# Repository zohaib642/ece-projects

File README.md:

# ece-projects

**Street Fighter (MSPM0G3507 Embedded Game)**
A 1v1 fighting game running on a custom PCB designed in KiCad and hand-soldered. Built around the MSPM0G3507 microcontroller with custom hardware drivers and a 30 Hz game engine running on a TimerG12 ISR. Player movement is driven by a slidepot ADC channel, a 2-axis analog joystick handles jumping, and four external buttons map to punch, kick, block, and pause. Sampled audio plays through a 5-bit DAC over an 11 kHz SysTick interrupt, providing background music and event-driven sound effects (hit, block, KO). Features include 16-bit color sprite rendering on an ST7735 LCD with edge-only erase to minimize flicker, an enemy AI with attack/block/movement states, real-time HP and score tracking, and bilingual (English/Spanish) UI selectable at startup.

**Programmable Stopwatch/Timer (Verilog on Basys3 FPGA)**
A four-mode digital stopwatch and countdown timer implemented in Verilog using RTL-design methodology and deployed to a Digilent Basys3 FPGA. Designed via HLSM formalism with a custom datapath and controller FSM. Supports counting up from 00.00, counting down from 99.99, and externally loaded variants where the initial seconds value is set through eight onboard switches. Time is shown across four seven-segment displays at 10 ms resolution, with two pushbuttons for start/stop and reset and two mode-select switches. Built and verified in Xilinx Vivado.

**Buck Converter (PWM Control)**
Design and analysis of a DC-DC buck converter circuit using PWM control. Explores the relationship between switching frequency (50-100 kHz), duty cycle, and output voltage regulation. Includes current sensing measurements and characterization of the linear relationship between op-amp output and load voltage.

**Stone Game (LC-3 Assembly)**
A two-player Nim-style strategy game implemented in LC-3 assembly language. Players alternate removing stones from three rows (A, B, C), with the player who takes the last stone winning. Features input validation, game state management, and a complete turn-based game loop.

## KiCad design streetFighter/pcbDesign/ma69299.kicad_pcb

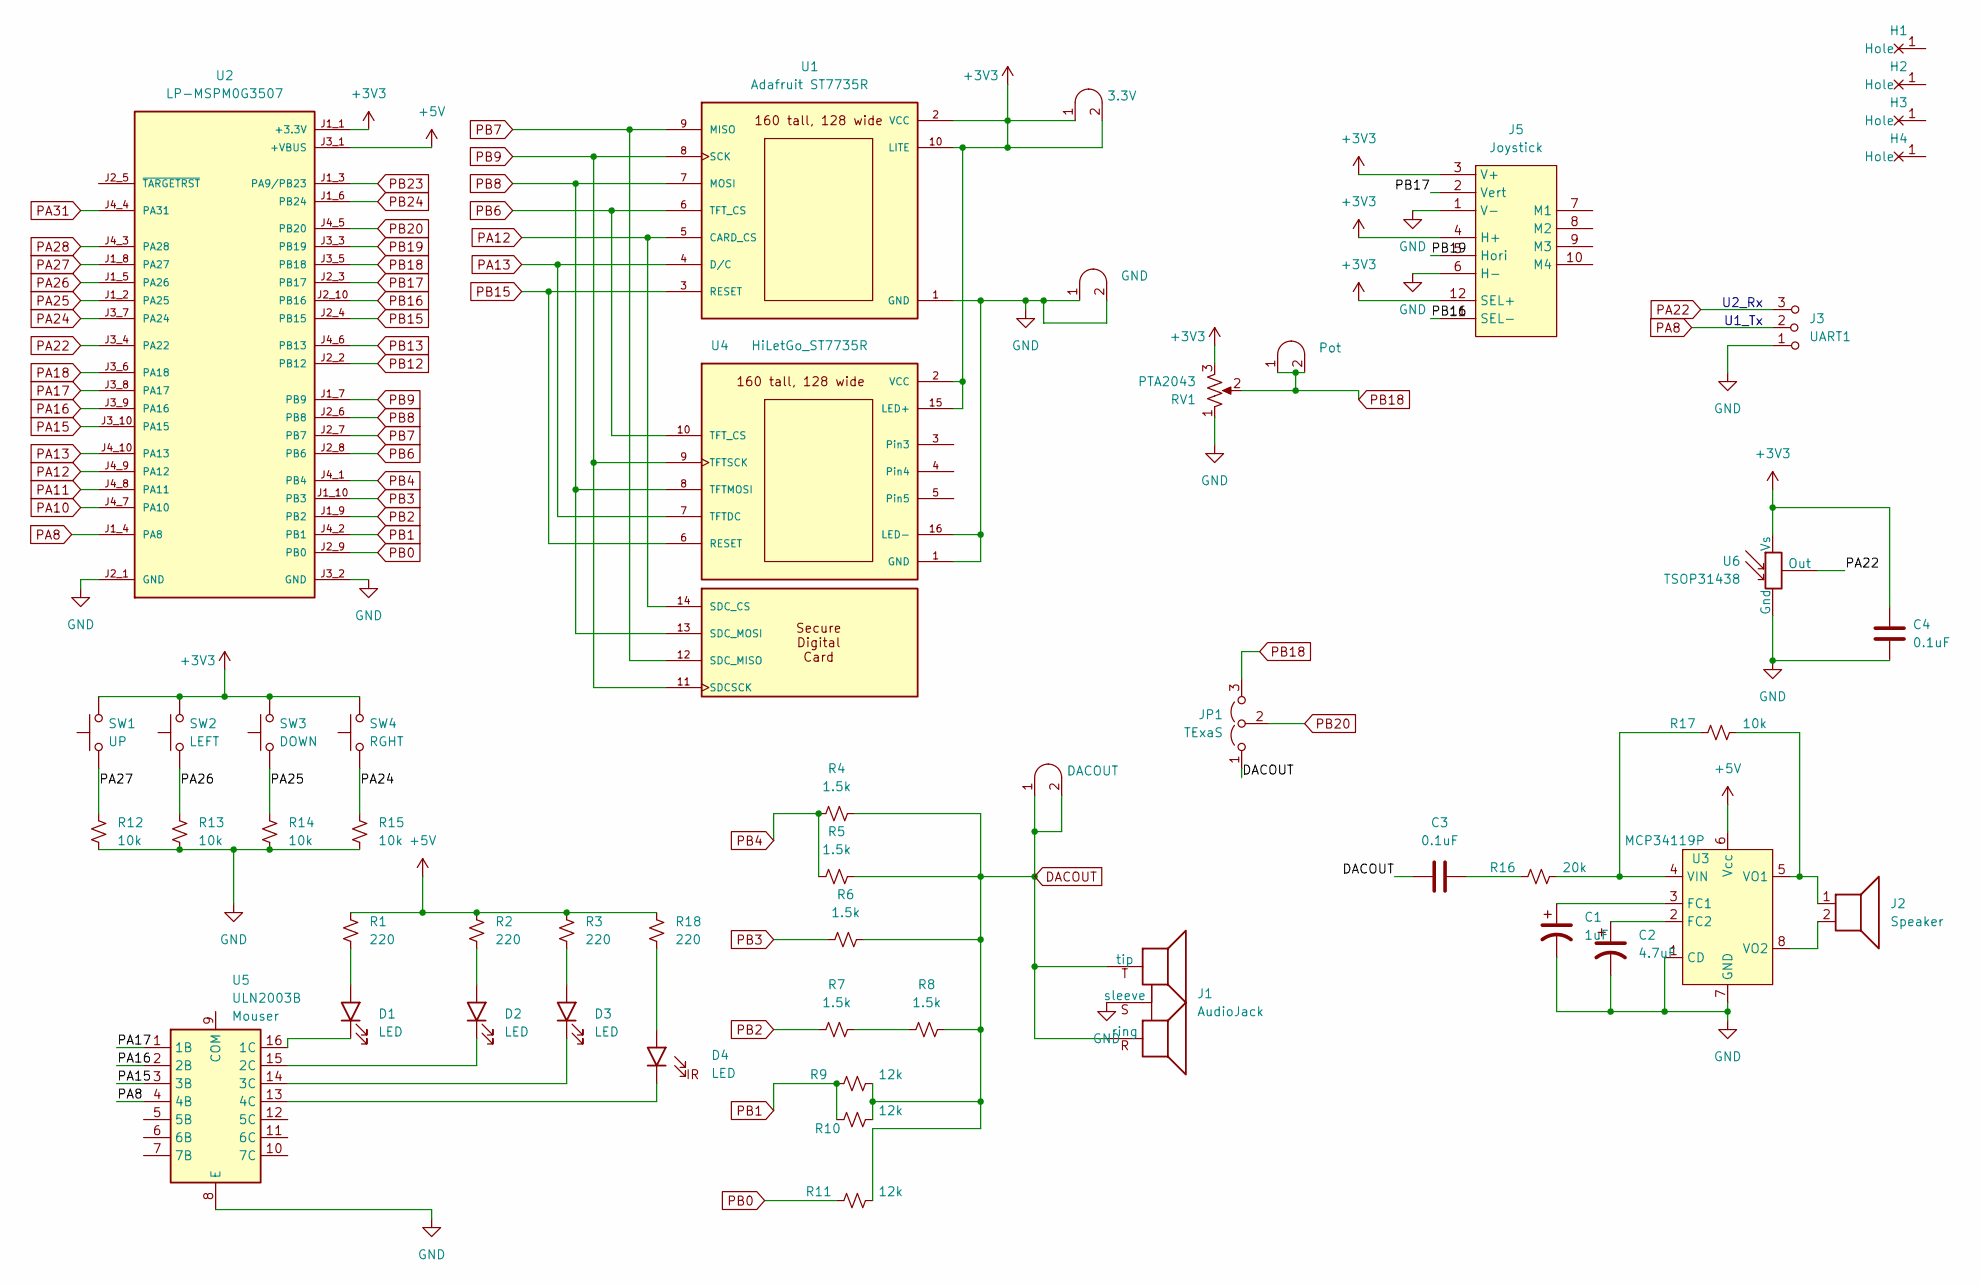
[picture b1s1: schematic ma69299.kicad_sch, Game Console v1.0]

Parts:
C1: 1uF; CP_Radial_Tantal200mil
C2: 4.7uF; CP_Radial_Tantal200mil
C3, C4: 0.1uF; C_Axial_200mil
D1, D2, D3, D4: LED; LED_D5.0mm
H1, H2, H3, H4: MountingHole_4_40
J1: AudioJack; Jack_3.5mm_CUI_SJ1-3523N_Horizontal
J2: Speaker; PinHeader_1x02_P2.54mm_Vertical
J3: UART1; PinHeader_1x03_P2.54mm_Vertical
J4: Pot; Testpoint_1x02_P2.54mm
J5: Joystick; SparkfunJoystick
J6: GND; Testpoint_1x02_P2.54mm
J7: DACOUT; Testpoint_1x02_P2.54mm
JP1: TExaS; PinHeader_1x03_P2.54mm_Vertical
R1, R2, R3, R18: 220; R_Axial_DIN0204_L3.6mm_D1.6mm_P7.62mm_Horizontal
R4, R5, R6, R7, R8: 1.5k; R_Axial_DIN0204_L3.6mm_D1.6mm_P7.62mm_Horizontal
R9, R10, R11: 12k; R_Axial_DIN0204_L3.6mm_D1.6mm_P7.62mm_Horizontal
R12, R13, R14, R15, R17: 10k; R_Axial_DIN0204_L3.6mm_D1.6mm_P7.62mm_Horizontal
R16: 20k; R_Axial_DIN0204_L3.6mm_D1.6mm_P7.62mm_Horizontal
RV1: PTA2043; PTA2043pot
SW1: UP; SW_PUSH_6mm
SW2: LEFT; SW_PUSH_6mm
SW3: DOWN; SW_PUSH_6mm
SW4: RGHT; SW_PUSH_6mm
TP1: 3.3V; Testpoint_1x02_P2.54mm
U1: Adafruit ST7735R; adafruit_st7735r
U2: LP-MSPM0G3507; ti_LP_MSPM0G3507
U3: MCP34119P; DIP-8_W7.62mm_LongPads
U4: HiLetGo_ST7735R; hiletgo_st7735r
U5: ULN2003B; DIP-16_W7.62mm
U6: TSOP31438

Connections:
+3V3: C4.1, J5.3 (V+), J5.4 (H+), J5.12 (SEL+), RV1.3, SW1.2, SW2.2, SW3.2, SW4.2, TP1.1 (A), TP1.2 (B), U1.2 (VCC), U1.10 (LITE), U2.J1_1 (+3.3V), U4.2 (VCC), U4.15 (LED+), U6.2 (Vs)
+5V: R1.1, R2.1, R3.1, R18.1, U2.J3_1 (+VBUS), U3.6 (Vcc)
DACOUT: C3.1, J1.R (ring), J1.T (tip), J7.1 (A), J7.2 (B), JP1.1 (A), R4.1, R5.1, R6.1, R8.1, R9.1, R10.1, R11.1
GND: C1.2, C2.2, C4.2, J1.S (sleeve), J3.1 (A), J5.1 (V-), J5.6 (H-), J6.1 (A), J6.2 (B), R12.2, R13.2, R14.2, R15.2, RV1.1, U1.1 (GND), U2.J2_1 (GND), U2.J3_2 (GND), U3.1 (CD), U3.7 (GND), U4.1 (GND), U4.16 (LED-), U5.8 (E), U6.1 (Gnd)
unnamed: C3.2, R16.2
unnamed: D1.2 (A), R1.2
unnamed: D1.1 (K), U5.16 (1C)
unnamed: D2.2 (A), R2.2
unnamed: D2.1 (K), U5.15 (2C)
unnamed: D3.2 (A), R3.2
unnamed: D3.1 (K), U5.14 (3C)
unnamed: D4.2 (A), R18.2
unnamed: D4.1 (K), U5.13 (4C)
unnamed: R7.1, R8.2
unnamed: C1.1, U3.3 (FC1)
unnamed: C2.1, U3.2 (FC2)
unnamed: R16.1, R17.2, U3.4 (VIN)
unnamed: J2.1, R17.1, U3.5 (VO1)
unnamed: J2.2, U3.8 (VO2)
PA8: J3.2 (B), U2.J1_4 (PA8), U5.4 (4B)
PA10: U2.J4_7 (PA10)
PA11: U2.J4_8 (PA11)
PA12: U1.5 (CARD_CS), U2.J4_9 (PA12), U4.14 (SDC_CS)
PA13: U1.4 (D/C), U2.J4_10 (PA13), U4.7 (TFTDC)
PA15: U2.J3_10 (PA15), U5.3 (3B)
PA16: U2.J3_9 (PA16), U5.2 (2B)
PA17: U2.J3_8 (PA17), U5.1 (1B)
PA18: U2.J3_6 (PA18)
PA22: J3.3 (C), U2.J3_4 (PA22), U6.3 (Out)
PA24: R15.1, SW4.1, U2.J3_7 (PA24)
PA25: R14.1, SW3.1, U2.J1_2 (PA25)
PA26: R13.1, SW2.1, U2.J1_5 (PA26)
PA27: R12.1, SW1.1, U2.J1_8 (PA27)
PA28: U2.J4_3 (PA28)
PA31: U2.J4_4 (PA31)
PB0: R11.2, U2.J2_9 (PB0)
PB1: R9.2, R10.2, U2.J4_2 (PB1)
PB2: R7.2, U2.J1_9 (PB2)
PB3: R6.2, U2.J1_10 (PB3)
PB4: R4.2, R5.2, U2.J4_1 (PB4)
PB6: U1.6 (TFT_CS), U2.J2_8 (PB6), U4.10 (TFT_CS)
PB7: U1.9 (MISO), U2.J2_7 (PB7), U4.12 (SDC_MISO)
PB8: U1.7 (MOSI), U2.J2_6 (PB8), U4.8 (TFTMOSI), U4.13 (SDC_MOSI)
PB9: U1.8 (SCK), U2.J1_7 (PB9), U4.9 (TFTSCK), U4.11 (SDCSCK)
PB12: U2.J2_2 (PB12)
PB13: U2.J4_6 (PB13)
PB15: U1.3 (RESET), U2.J2_4 (PB15), U4.6 (RESET)
PB16: J5.11 (SEL-), U2.J2_10 (PB16)
PB17: J5.2 (Vert), U2.J2_3 (PB17)
PB18: J4.1 (A), J4.2 (B), JP1.3 (B), RV1.2, U2.J3_5 (PB18)
PB19: J5.5 (Hori), U2.J3_3 (PB19)
PB20: JP1.2 (C), U2.J4_5 (PB20)
PB23: U2.J1_3 (PA9/PB23)
PB24: U2.J1_6 (PB24)

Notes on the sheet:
U2_Rx
U1_Tx

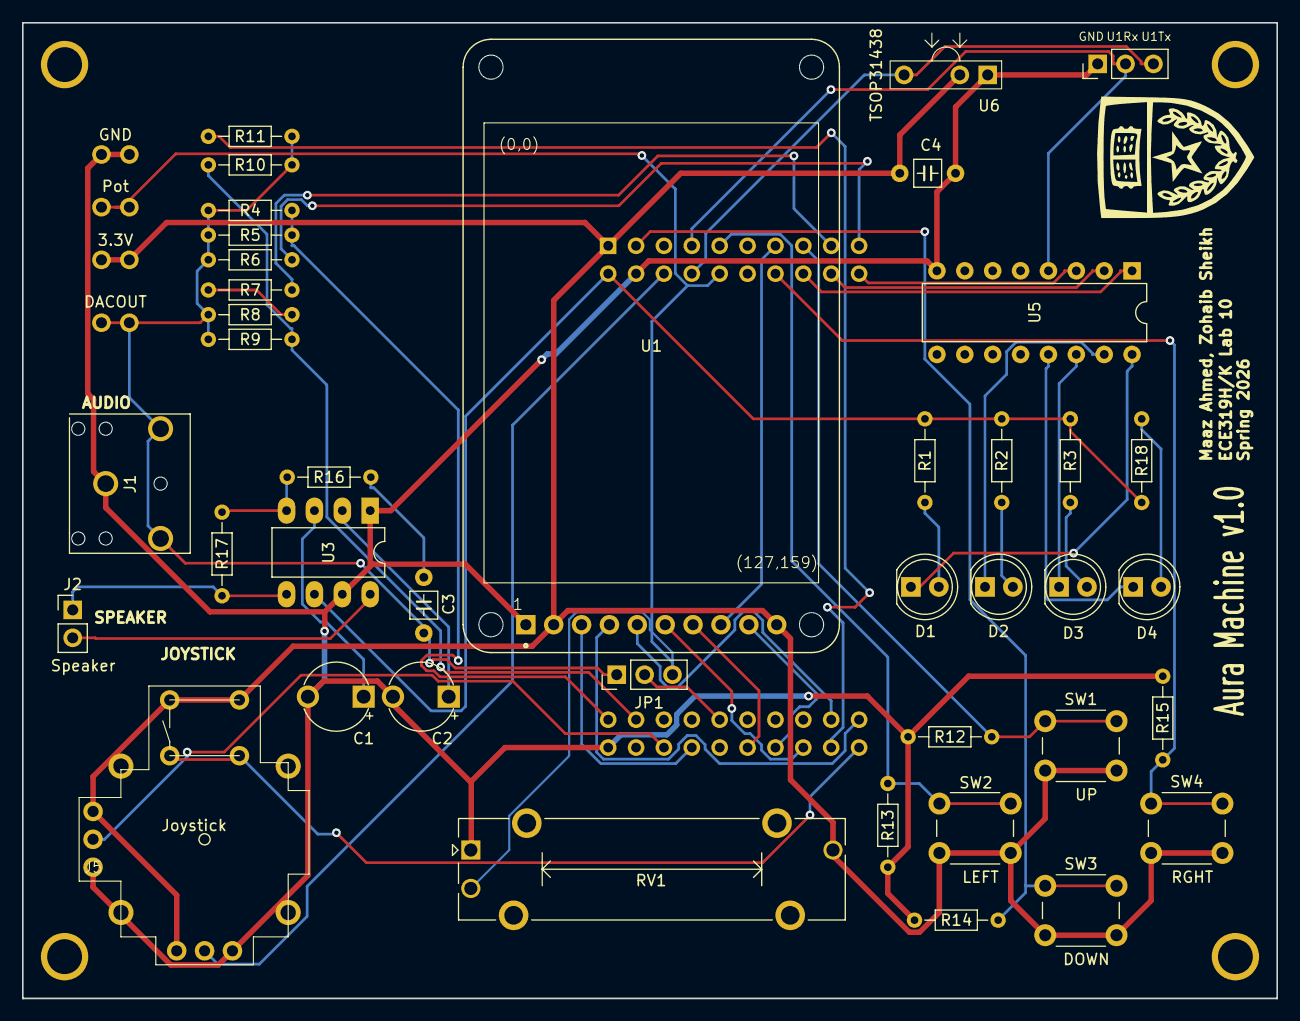
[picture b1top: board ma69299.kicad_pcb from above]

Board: 2 copper layers, 114.3 x 88.9 mm, 49 parts (1 on the bottom side), 45 nets.

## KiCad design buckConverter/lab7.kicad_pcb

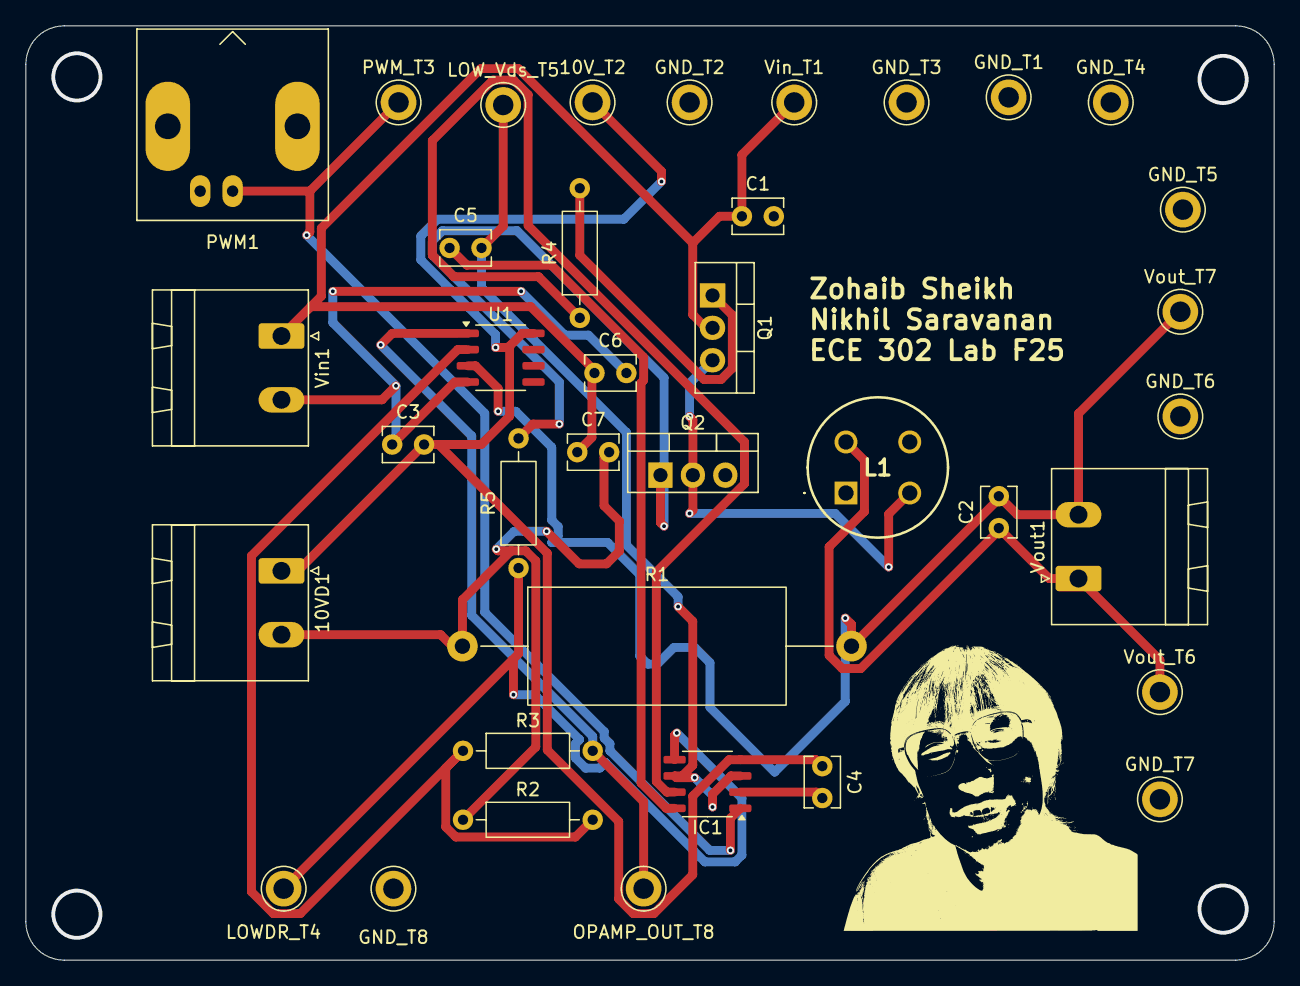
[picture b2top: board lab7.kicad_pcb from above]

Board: 2 copper layers, 97.8 x 73.2 mm, 37 parts (0 on the bottom side), 15 nets.

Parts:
10VD1: Screw_Terminal_01x02; PhoenixContact_MSTBA_2,5_2-G_1x02_P5.00mm_Horizontal
10V_T2: TestPoint; TestPoint_Keystone_5010-5014_Multipurpose
C1, C6, C7: 10u; C_Disc_D3.8mm_W2.6mm_P2.50mm
C2, C3, C4, C5: 1u; C_Disc_D3.8mm_W2.6mm_P2.50mm
GND_T1, GND_T2, GND_T3, GND_T4, GND_T5, GND_T6, GND_T7, GND_T8: TestPoint; TestPoint_Keystone_5010-5014_Multipurpose
IC1: TPS2832D; SO-8_3.9x4.9mm_P1.27mm
L1: 7447231101
LOWDR_T4: TestPoint; TestPoint_Keystone_5010-5014_Multipurpose
LOW_Vds_T5: TestPoint; TestPoint_Keystone_5010-5014_Multipurpose
OPAMP_OUT_T8: TestPoint; TestPoint_Keystone_5010-5014_Multipurpose
PWM1: Conn_Coaxial; BNC_Amphenol_B6252HB-NPP3G-50_Horizontal
PWM_T3: TestPoint; TestPoint_Keystone_5010-5014_Multipurpose
Q1, Q2: CSD18534KCS; TO-220-3_Vertical
R1: 0.5; R_Axial_DIN0922_L20.0mm_D9.0mm_P30.48mm_Horizontal
R2: 5k; R_Axial_DIN0207_L6.3mm_D2.5mm_P10.16mm_Horizontal
R3: 20k; R_Axial_DIN0207_L6.3mm_D2.5mm_P10.16mm_Horizontal
R4, R5: 100; R_Axial_DIN0207_L6.3mm_D2.5mm_P10.16mm_Horizontal
U1: TLV2372; SO-8_3.9x4.9mm_P1.27mm
Vin1: Screw_Terminal_01x02; PhoenixContact_MSTBA_2,5_2-G_1x02_P5.00mm_Horizontal
Vin_T1: TestPoint; TestPoint_Keystone_5010-5014_Multipurpose
Vout1: Screw_Terminal_01x02; PhoenixContact_MSTBA_2,5_2-G_1x02_P5.00mm_Horizontal
Vout_T6, Vout_T7: TestPoint; TestPoint_Keystone_5010-5014_Multipurpose

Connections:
5W: L1.2, Q1.3 (S), Q2.2 (D)
10V: 10VD1.1, 10V_T2.1, C3.2, C4.1, IC1.4 (VCC), U1.8 (V+)
BOOT: C5.1, IC1.8 (BOOT)
GND: 10VD1.2, C1.2, C3.1, C4.2, C6.2, C7.2, GND_T1.1, GND_T2.1, GND_T3.1, GND_T4.1, GND_T5.1, GND_T6.1, GND_T7.1, GND_T8.1, IC1.2 (PGND), PWM1.2 (Ext), Q2.3 (S), R1.1, R2.1, U1.4 (V-), Vin1.2
HIGHDR: IC1.7 (HIGHDR), R4.1
LOWDR: IC1.5 (LOWDR), LOWDR_T4.1, R5.1
unnamed: Q1.1 (G), R4.2
unnamed: Q2.1 (G), R5.2
unnamed: R2.2, R3.1, U1.2 (-)
OPAMP_OUT: OPAMP_OUT_T8.1, R3.2, U1.1
PWM: IC1.1 (IN), PWM1.1 (In), PWM_T3.1
SW: C5.2, IC1.3 (DT), IC1.6 (BOOTLO), LOW_Vds_T5.1
Vin+: C1.1, C6.1, C7.1, Q1.2 (D), Vin1.1, Vin_T1.1
Vout+: C2.1, L1.3, Vout1.1, Vout_T6.1
Vout-: C2.2, R1.2, U1.3 (+), Vout1.2, Vout_T7.1

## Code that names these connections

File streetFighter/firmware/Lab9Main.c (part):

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volatile uint32_t MusicMuteFrames=0;
volatile int32_t PrevPlayerHP=-1;
volatile int32_t PrevEnemyHP=-1;
#define LED_HIT_ENEMY LED_BLOCK   // PA15
#define LED_HIT_PLAYER LED_PUNCH  // PA17
volatile uint32_t GreenLEDTimer = 0;
volatile uint32_t RedLEDTimer = 0;

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    uint32_t now = Switch_In();
    LED_Off(LED_PUNCH|LED_KICK|LED_BLOCK|LED_PAUSE);

    if(now & 0x01){        // PA24
      LED_On(LED_PAUSE);   // PA8
    }
    if(now & 0x02){        // PA25
      LED_On(LED_BLOCK);   // PA15
    }
    if(now & 0x04){        // PA26
      LED_On(LED_KICK);    // PA16
    }
    if(now & 0x08){        // PA27
      LED_On(LED_PUNCH);   // PA17
    }
  }
}
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  Switch_Init(); // initialize switches
  LED_Init(); // initialize LED
  Sound_Init();  // initialize sound
  TExaS_Init(ADC0,6,0); // ADC1 channel 6 is PB20, TExaS scope
  __enable_irq();
  while(1){
    now = Switch_In(); // one of your buttons
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  LaunchPad_Init();
  ST7735_InitPrintf(INITR_REDTAB); // INITR_REDTAB for AdaFruit, INITR_BLACKTAB for HiLetGo
  ST7735_FillScreen(ST7735_BG);
  ADCinit();     //PB18 = ADC1 channel 5, slidepot
  Switch_Init(); // initialize switches
  LED_Init();    // initialize LED
  Sound_Init();  // initialize sound
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
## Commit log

2025-12-23 Enhance README with project details
    Added project descriptions for Buck Converter and Stone Game.
2025-12-23 Update project title in README
    Removed author name from the project title in README.
2026-05-09 Update README with project descriptions
    Added descriptions for Street Fighter and Programmable Stopwatch/Timer projects.
2026-05-09 Added stopwatch project
2026-05-09 Added street fighter project
